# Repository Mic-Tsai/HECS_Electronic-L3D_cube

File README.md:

## L3D_cube_4x4x4

Use the microphone to design an interactive experience.
You will figure out the LEDs will start dancing with the music!

```
Arduino tool kit, and require following breakout board:
- MCU: Arduino 
- Display: WS2812B-5050
- Power source: Li-Po Battery
```

##

### **About Mic**

Director of HECS, design light painting product which contains hardware layout and software programming.

- [Resume](https://drive.google.com/file/d/1NEWwNo3X4ogJMNzp6jpFyT0a6GPGhs7Q/view)

## 

### **About HECS**

If you interesting how it works please refer for detail:

- [HECS Electronics](https://drive.google.com/file/d/1tgr780FQ_Ib0JO3FdQn_M6LVbDeVmUmG/view?usp=sharing)

## 

If you want to buy this board and are in Taiwan, please visit my shop: 

Will OPEN SOON:
* [HECS SHOP](https://www.)
* Contact me via mail (xbcke12345@gmail.com)
* If this project helping. Please generously support =)

##

## 

>### License Information
>>This product is open source! Both, our hardware and software are open source and licensed under the following:
>>#### Hardware
>>>All hardware is released under [Creative Commons Share-alike 4.0 International](http://creativecommons.org/licenses/by-sa/4.0/)
>>#### Software 
>>>All software is released under the MIT License [http://opensource.org/licenses/MIT](http://opensource.org/licenses/MIT)
>>#### Documentation
>>>The documentation on this page is released under [Creative Commons Share-alike 4.0 International](http://creativecommons.org/licenses/by-sa/4.0/)

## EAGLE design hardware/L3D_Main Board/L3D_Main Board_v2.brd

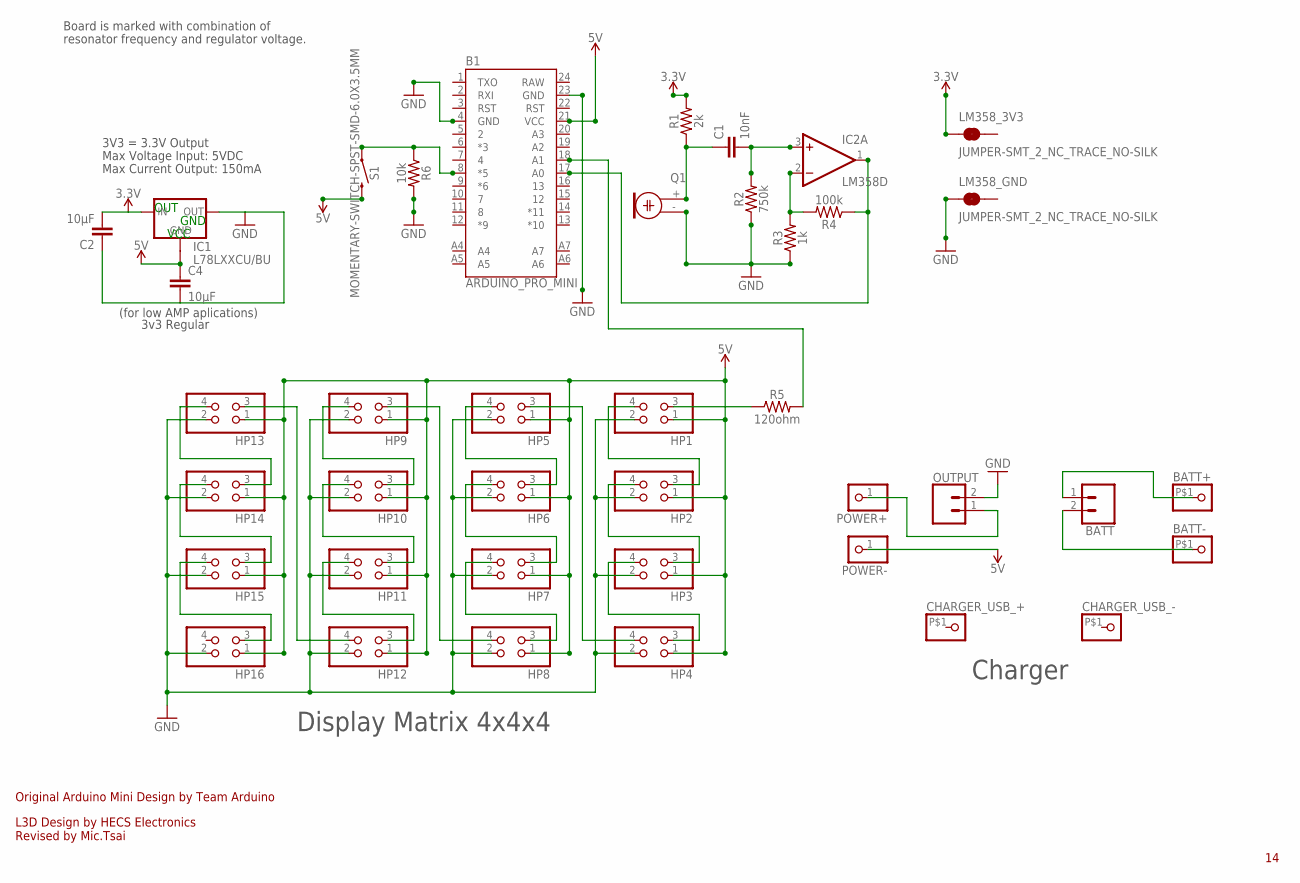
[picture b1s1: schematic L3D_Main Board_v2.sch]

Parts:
B1: ARDUINO_PRO_MINI
BATT: CONN_02; 1X02
BATT+: PINHD-1X1-BIGPOGO; 1X1-BIGPOGO
BATT-: PINHD-1X1-BIGPOGO; 1X1-BIGPOGO
C1: 10nF; 0805
C2, C4: 10µF; 0805
CHARGER_USB_+: PINHD-1X1-BIGPOGO; 1X1-BIGPOGO
CHARGER_USB_-: PINHD-1X1-BIGPOGO; 1X1-BIGPOGO
HP1, HP2, HP3, HP4, HP5, HP6, HP7, HP8, HP9, HP10, HP11, HP12, HP13, HP14, HP15, HP16: PINHD-2X2_2.00; 2X02M
IC1: L78LXXCU/BU; SOT89
IC2: LM358D; SO08
LM358_3V3, LM358_GND: JUMPER-SMT_2_NC_TRACE_NO-SILK; SMT-JUMPER_2_NC_TRACE_NO-SILK
OUTPUT: CONN_02; 1X02
POWER+: PINHD-1X1; 1X01
POWER-: PINHD-1X1; 1X01
Q1: ELECTRET; 9.7ELECTRET
R1: 2k; 0603
R2: 750k; 0603
R3: 1k; 0603
R4: 100k; 0603
R5: 120ohm; 1210
R6: 10k; 0603
S1: MOMENTARY-SWITCH-SPST-SMD-6.0X3.5MM; TACTILE_SWITCH_SMD_6.0X3.5MM

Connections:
3.3V: C2.2, IC1.3 (IN), LM358_3V3.1, R1.2
5V: B1.21 (VCC), C4.1, HP1.1, HP2.1, HP3.1, HP4.1, HP5.1, HP6.1, HP7.1, HP8.1, HP9.1, HP10.1, HP11.1, HP12.1, HP13.1, HP14.1, HP15.1, HP16.1, IC1.4 (GND1), POWER-.1, S1.2
GND: B1.4 (GND), B1.23 (GND), C2.1, C4.2, HP1.2, HP2.2, HP3.2, HP4.2, HP5.2, HP6.2, HP7.2, HP8.2, HP9.2, HP10.2, HP11.2, HP12.2, HP13.2, HP14.2, HP15.2, HP16.2, IC1.1 (OUT), LM358_GND.1, OUTPUT.2, Q1.- (1), R2.1, R3.1, R6.2
unnamed: C1.2, IC2.3 (+IN), R2.2
unnamed: C1.1, Q1.+ (2), R1.1
unnamed: IC2.2 (-IN), R3.2, R4.2
unnamed: HP1.4, HP2.3
unnamed: HP2.4, HP3.3
unnamed: HP3.4, HP4.3
unnamed: HP4.4, HP5.3
unnamed: HP5.4, HP6.3
unnamed: HP6.4, HP7.3
unnamed: HP7.4, HP8.3
unnamed: HP8.4, HP9.3
unnamed: HP9.4, HP10.3
unnamed: HP10.4, HP11.3
unnamed: HP11.4, HP12.3
unnamed: HP12.4, HP13.3
unnamed: HP13.4, HP14.3
unnamed: HP14.4, HP15.3
unnamed: HP15.4, HP16.3
unnamed: B1.17 (A0), IC2.1 (OUT), R4.1
unnamed: B1.8 (*5), R6.1, S1.1
unnamed: OUTPUT.1, POWER+.1
unnamed: B1.18 (A1), R5.2
unnamed: HP1.3, R5.1
unnamed: BATT.1, BATT+.P$1
unnamed: BATT.2, BATT-.P$1
RAW: B1.24 (RAW)
V+: IC2.8 (V+)
V-: IC2.4 (V-)

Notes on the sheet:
L3D Design by HECS Electronics Revised by Mic.Tsai
Original Arduino Mini Design by Team Arduino
Max Voltage Input: 5VDC
Max Current Output: 150mA
Board is marked with combination of
resonator frequency and regulator voltage.
3V3 = 3.3V Output
3v3 Regular
(for low AMP aplications)
OUT
GND
VCC
Display Matrix 4x4x4
Charger

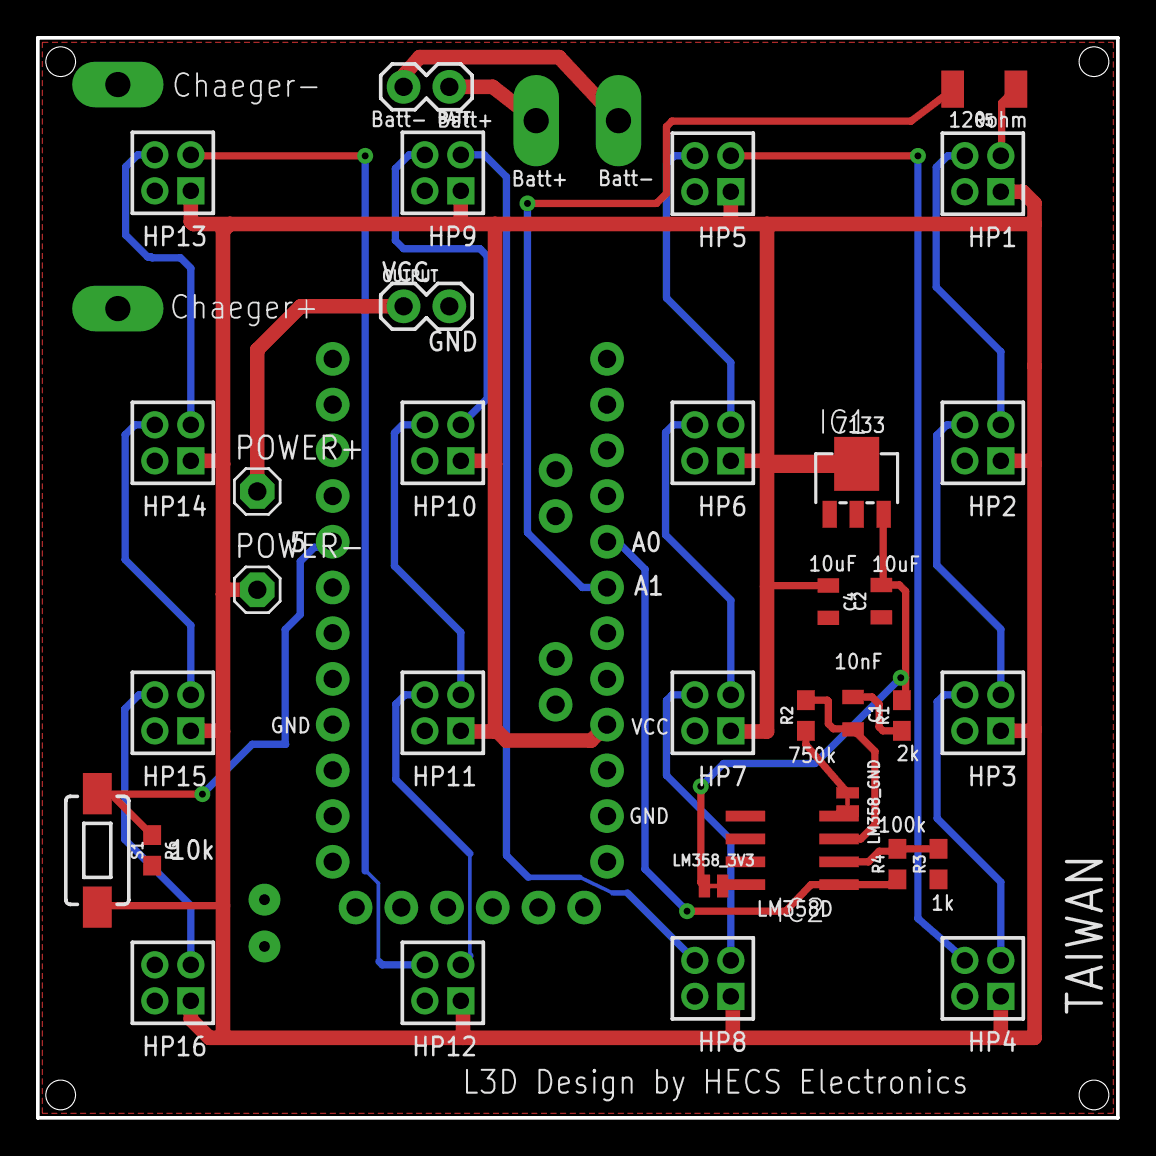
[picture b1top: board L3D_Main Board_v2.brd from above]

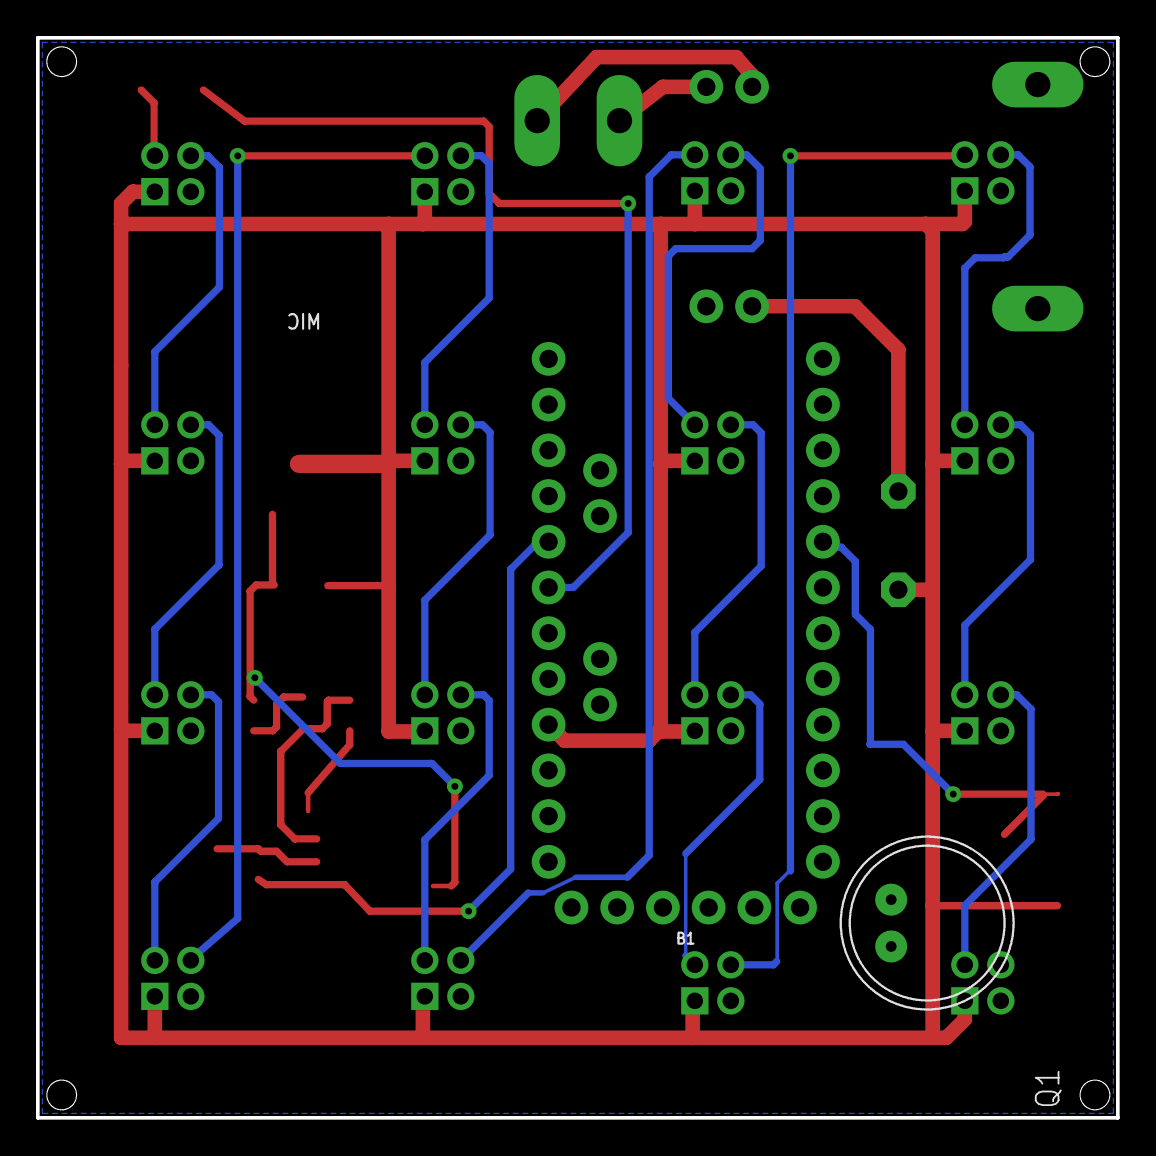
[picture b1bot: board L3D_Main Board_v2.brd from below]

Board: 2 copper layers, 60.0 x 60.0 mm, 40 parts (4 on the bottom side), 28 nets.

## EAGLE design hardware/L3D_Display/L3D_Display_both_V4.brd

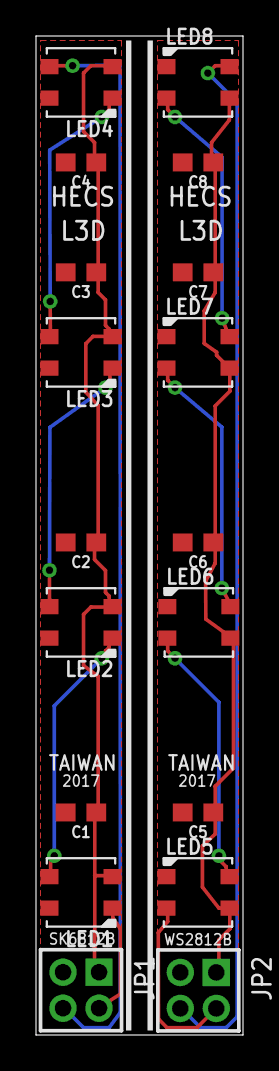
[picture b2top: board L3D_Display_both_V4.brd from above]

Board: 2 copper layers, 11.5 x 55.5 mm, 18 parts (0 on the bottom side), 14 nets.

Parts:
C1, C2, C3, C4, C5, C6, C7, C8: 0.1uF; 0603
JP1, JP2: 2X02M
LED1, LED2, LED3, LED4, LED5, LED6, LED7, LED8: WS2812B3535; LED3535

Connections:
+5V: C1.1, C2.1, C3.1, C4.1, JP1.1, LED1.2, LED2.2, LED3.2, LED4.2
COM: C1.2, C2.2, C3.2, C4.2, JP1.3, LED1.4, LED2.4, LED3.4, LED4.4
GNDA: C5.2, C6.2, C7.2, C8.2, JP2.3, LED5.1, LED6.1, LED7.1, LED8.1
unnamed: JP1.4, LED4.3
unnamed: LED1.3, LED2.1
unnamed: LED2.3, LED3.1
unnamed: LED3.3, LED4.1
unnamed: LED5.4, LED6.2
unnamed: JP1.2, LED1.1
unnamed: LED6.4, LED7.2
unnamed: LED7.4, LED8.2
unnamed: JP2.2, LED5.2
unnamed: JP2.4, LED8.4
VCC/2: C5.1, C6.1, C7.1, C8.1, JP2.1, LED5.3, LED6.3, LED7.3, LED8.3

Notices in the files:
parts and their libraries:
SparkFun-Capacitors: Licensing: Creative Commons ShareAlike 4.0 International - https://creativecommons.org/licenses/by-sa/4.0
